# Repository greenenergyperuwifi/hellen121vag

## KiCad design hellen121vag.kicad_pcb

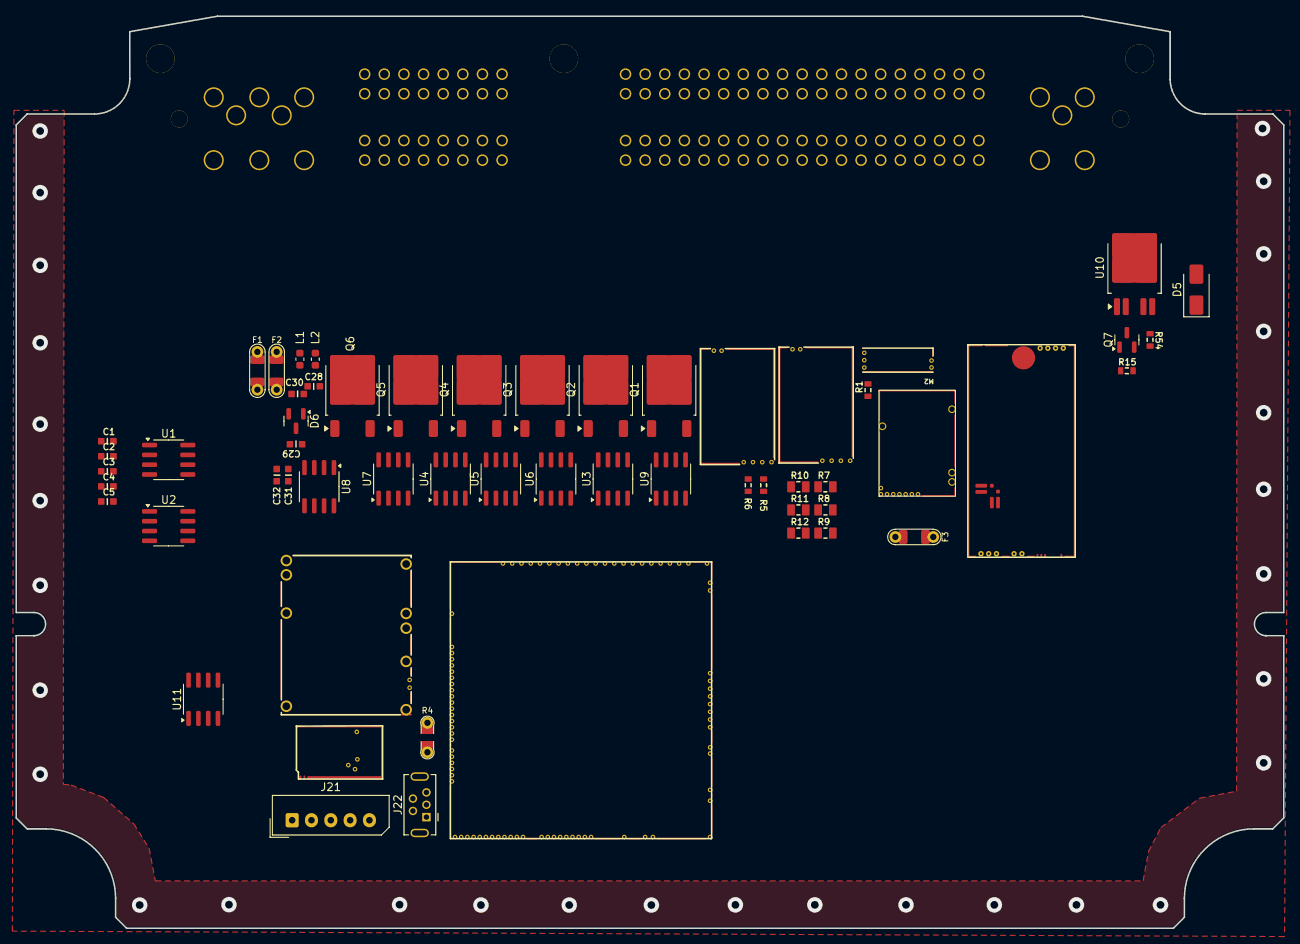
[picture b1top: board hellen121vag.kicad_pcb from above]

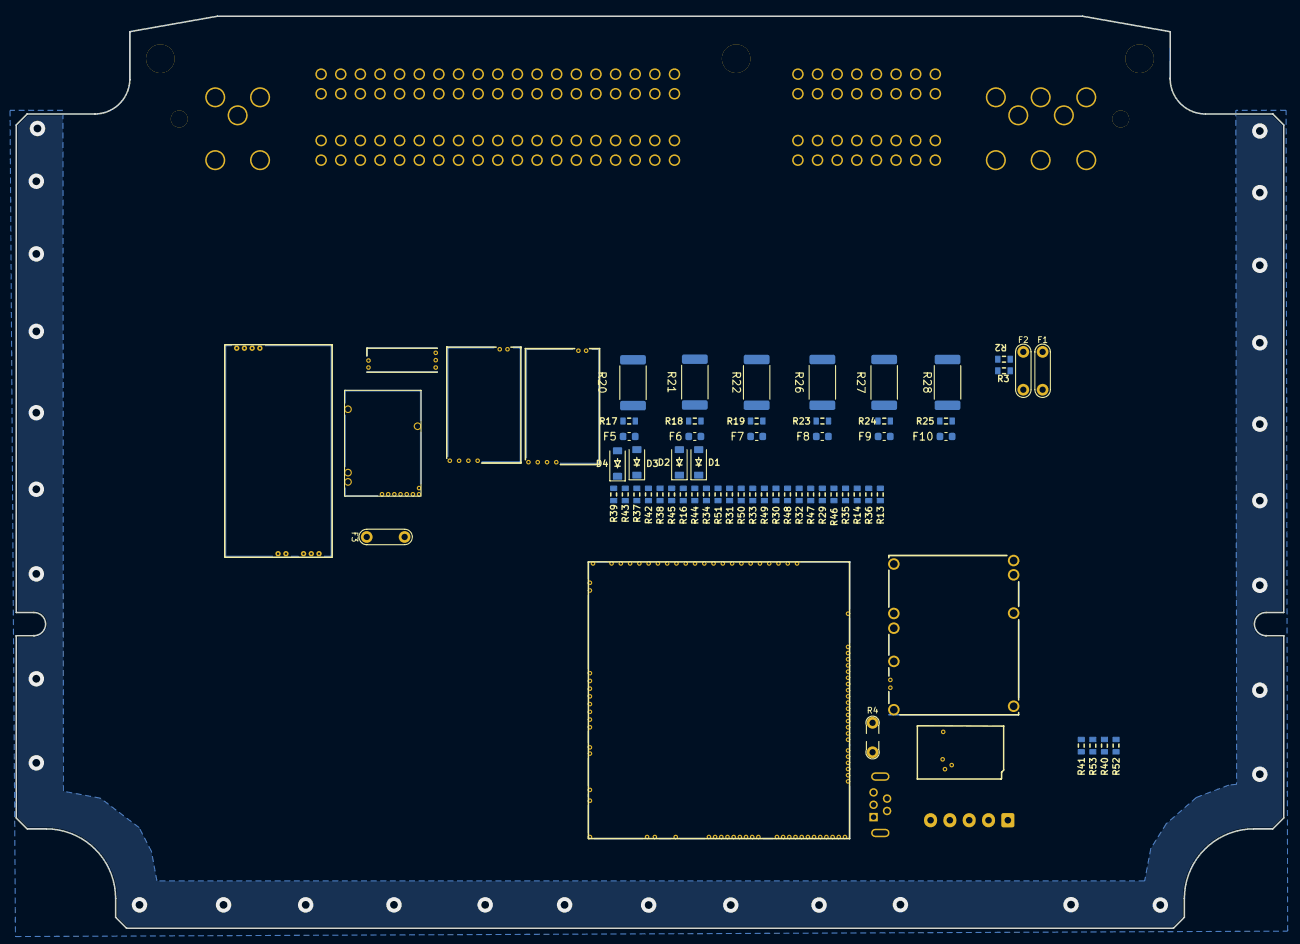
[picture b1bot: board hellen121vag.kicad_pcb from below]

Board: 4 copper layers, 164.0 x 118.0 mm, 110 parts (52 on the bottom side), 142 nets, no tracks yet.

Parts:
C1, C3, C28, C30: 10n; C0603
C2, C4, C29, C31: 100n; C0603
C5, C32: 1u; C0603
D1, D2, D3, D4: B5819W; SOD-123
D5: SS34; D_SMA
D6: NUP2105L; SOT-23
F1, F2, F3: 12H1500D; PAD-1206-PAD
F5, F6, F7, F8, F9, F10: 50mA; Fuse_0603_1608Metric
J21: Conn_01x05_Male; Molex_SPOX_5267-05A_1x05_P2.50mm_Vertical
J22: USB_B_Mini; USB-MINI-B-VERTICAL
L1, L2: 470R@100MHz; L_0603_1608Metric
M1: Module-power_12and5V-0.3; power_12and5V
M2: Module-knock-0.2; knock
M3: Module-vr-discrete-0.5; vr-discrete
M4: Module-vr-max9924-0.1; vr-max9924
M5: Module-wbo-0.5; wbo
M6: Module:mega-mcu100/0.3; mega-mcu100
M7: Module-can-0.1; can
M8: Module-motor-driver-0.1; motor-driver
P1: 368255-2
Q1, Q2, Q3, Q4, Q5: ISL9V3040D3ST; TO-252-2
Q6: AO3400A; TO-252-2
Q7: AO3400A; SOT-23
R1, R13, R14, R15, R16, R17, R29, R30, R31, R32, R33, R34, R35, R36, R37, R38, R39, R40, R41, R42, R43, R44, R45, R46, R47, R50, R51, R52, R53: 4.7k; R0603
R2: 33k; R0603
R3: 6.8k; R0603
R4: Jumper-Pad-Pad; PAD-0805-PAD
R5, R6, R19, R25: 0; R0603
R7, R8, R9: DNP; R0805
R10, R11, R12: 10k; R0805
R18, R23, R24, R48, R49: 22; R0603
R20, R21, R26, R27: 0; R_2512_6332Metric
R22: 22; R_2512_6332Metric
R28: 4.7k; R_2512_6332Metric
R54: 1k; R0603
U1, U7, U8: MAX31855KASA; SOIC-8_3.9x4.9mm_P1.27mm
U2, U3, U4, U5, U6, U9, U11: VNLD5160TR-E; SOIC-8_3.9x4.9mm_P1.27mm
U10: BTS6143D; TO-252-4

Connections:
+3.3V: M6.N21 (V33), M8.W5 (3V3_IN)
+3.3VA: C4.2, C5.2, C31.2, C32.2, M6.N15 (V33_SWITCHABLE), M7.V2 (CAN_VIO), U7.4 (V_CC), U8.4 (V_CC)
+5V: M1.E4 (V5), M6.N22 (VCC)
+5VA: M2.E1 (V5A), M3.E4 (V5_IN), M4.E4 (V5_IN), M5.W1 (V5_IN), M6.E1 (V5A_SWITCHABLE), M6.W2 (V5A_SWITCHABLE), M7.V1 (V5), R7.2, R8.2, R9.2
/ADC3: M6.S15 (IN_KNOCK_(PA2)), R5.2, R6.2
/DC1_DIR: M6.E21 (OUT_PWM4_(PC8)), M8.W4 (DIR)
/DC1_PWM: M6.E20 (OUT_PWM3_(PC7)), M8.W2 (PWM)
/EGT/SPI_CS: M6.N9 (SPI3_CS_(PA15)), U7.6 (~CS), U8.6 (~CS)
/IGN1: F5.2, M6.W10 (IGN1_(PC13))
/IGN2: F6.2, M6.W9 (IGN2_(PE5))
/IGN3: F7.2, M6.W8 (IGN3_(PE4))
/IGN4: F8.2, M6.W7 (IGN4_(PE3))
/IGN5: F9.2, M6.W6 (IGN5_(PE2))
/IGN6: F10.2, M6.W5 (IGN6_(PB8))
/INJ1: M6.E17 (OUT_INJ1_(PD3)), R34.1, R35.1
/INJ2: M6.E16 (OUT_INJ2_(PA9)), R36.1, R37.1
/INJ3: M6.E15 (OUT_INJ3_(PD11)), R38.1, R39.1
/INJ4: M6.E14 (OUT_INJ4_(PD10)), R40.1, R41.1
/INJ5: M6.E13 (OUT_INJ5_(PD2)), R42.1, R43.1, R50.1
/INJ6: M6.E12 (OUT_INJ6_(PA8)), R44.1, R45.1, R51.1
/IN_KNOCK: M2.E3 (OUT_KNOCK), R5.1
/IN_VIGN: F1.2, M1.V2 (IN_VIGN)
/IN_VMAIN: M6.S6 (IN_AUX4_(PC5)), R2.1, R3.2
/LS1: M6.E11 (OUT_INJ7_(PD15)), R16.1, R17.1
/LS2: M6.E10 (OUT_INJ8_(PD12)), R13.1, R14.1
/LS_HOT1: M6.W4 (IGN7_(PB9)), R48.1, R49.1
/LS_HOT2: M6.W3 (IGN8_(PE6)), R46.1, R47.1
/MISO3: M6.N11 (SPI3_MISO_(PC11)), U7.7 (SO), U8.7 (SO)
/PG_5VP: M6.N12 (SPI3_MOSI_(PC12)), R4.2
/PWR_EN: M1.E5 (EN_5VP), M6.N20 (OUT_PWR_EN_(PE10))
/SCK3: M6.N10 (SPI3_SCK_(PC10)), U7.5 (SCK), U8.5 (SCK)
/USB+: J21.3, J22.3 (D+), M6.N3 (USBP_(PA12))
/USB-: J21.2, J22.2 (D-), M6.N2 (USBM_(PA11))
/VBAT: M1.E1 (VBAT), M6.N17 (VBAT)
/VBUS: J21.1, J22.1 (VBUS), M6.N1 (VBUS)
/VIGN: M1.E3 (VIGN), M6.E5 (IN_VIGN_(PA5))
/VREF1: M2.W2 (VREF), M6.S22 (VREF1)
/VR_DISCRETE: M3.E3 (OUT), M6.N18 (UART8_RX_(PE0))
/VR_DISCRETE_A: M3.E2 (OUT_A), R6.1
/VR_DISCRETE_THR: M3.E1 (Thresh_IN), M6.E23 (OUT_PWM6_(PD14))
/VR_MAX9924: M4.E3 (OUT), M6.N19 (UART8_TX_(PE1))
DC1_DIS_W1: M6.E8 (SPI2_MISO_(PB14)), M8.W1 (DIS)
E6INJ7CANRX: M6.E6 (SPI2_CS_/_CAN2_RX_(PB12)), M7.V6 (CAN_RX), R30.1, R33.1, R52.1
E7INJ8CANTX: M6.E7 (SPI2_SCK_/_CAN2_TX_(PB13)), M7.V5 (CAN_TX), R31.1, R32.1, R53.1
unnamed: F3.2, M8.N2 (12V_IN), M8.S1 (12V_IN)
unnamed: F5.1, R18.2, R21.1
unnamed: F6.1, R19.2, R22.1
unnamed: F7.1, R20.2, R23.1
unnamed: F8.1, R24.2, R27.1
unnamed: F9.1, R25.2, R28.1
unnamed: F10.1, R26.2, R29.1
unnamed: M1.E6 (PG_5VP), R4.1
unnamed: M5.J1 (SEL1), M5.J_GND1 (PULL_DOWN1)
unnamed: M6.N14a (LED_GREEN), Q7.1 (G), R15.1
unnamed: Q1.1 (G), R18.1
unnamed: Q2.1 (G), R19.1
unnamed: Q3.1 (G), R20.1
unnamed: Q4.1 (G), R24.1
unnamed: Q5.1 (G), R25.1
unnamed: Q6.1 (G), R26.1
unnamed: Q7.3 (D), U10.2 (IN)
unnamed: R13.2, U1.1 (IN1)
unnamed: R16.2, U1.3 (IN2)
unnamed: R30.2, U2.1 (IN1)
unnamed: R31.2, U2.3 (IN2)
unnamed: R39.2, U3.1 (IN1)
unnamed: R40.2, U3.3 (IN2)
unnamed: R42.2, U4.1 (IN1)
unnamed: R45.2, U4.3 (IN2)
unnamed: R35.2, U5.1 (IN1)
unnamed: R37.2, U5.3 (IN2)
unnamed: R46.2, R50.2, U6.1 (IN1)
unnamed: R48.2, R51.2, U6.3 (IN2)
unnamed: C2.2, C3.2, D6.2 (K), L1.2, U7.3 (T+)
unnamed: C1.2, C2.1, D6.1 (K), L2.2, U7.2 (T-)
unnamed: C29.2, C30.2, U8.3 (T+)
unnamed: C28.2, C29.1, U8.2 (T-)
unnamed: R54.1, U10.4 (IS)
unnamed: R52.2, U11.1 (IN1)
unnamed: R53.2, U11.3 (IN2)
PIN1: M8.S3 (OUT+), P1.1
PIN2: M8.S2 (OUT-), P1.2
PIN6: M6.N14 (UART2_RX_(PD6)), P1.6
PIN7: M6.N13 (UART2_TX_(PD5)), P1.7
PIN8: P1.8, Q6.2 (C), R29.2
PIN9: P1.9, Q4.2 (C), R27.2
PIN10: P1.10, Q3.2 (C), R23.2
PIN11: P1.11, Q5.2 (C), R28.2
PIN12: P1.12, Q2.2 (C), R22.2
PIN13: P1.13, Q1.2 (C), R21.2
PIN14: D1.2 (A), P1.14, U1.6 (D2)
PIN15: D2.2 (A), P1.15, U1.8 (D1)
PIN16: D3.2 (A), P1.16, U9.8 (D1)
PIN17: M3.W2 (VR+), P1.17
PIN18: M3.W1 (VR-), P1.18
PIN19: M4.W2 (VR+), P1.19
PIN20: M4.W1 (VR-), P1.20, R1.2
PIN21: L1.1, P1.21
PIN22: L2.1, P1.22
PIN34: M6.S2 (IN_D3_(PE14)), P1.34
PIN35: M6.S3 (IN_D2_(PE13)), P1.35
PIN36: M6.S4 (IN_D1_(PE12)), P1.36
PIN37: M6.S13 (IN_MAP1_(PC0)), P1.37
PIN38: M6.S18 (IN_TPS_(PA4)), P1.38
PIN39: M6.S9 (IN_AUX1_(PB0)), P1.39
PIN40: M6.S11 (IN_O2S_/_CAN_WAKEUP_(PA0)), P1.40
PIN41: M6.S10 (IN_O2S2_(PA1)), P1.41
PIN42: M6.S17 (IN_VSS_(PE11)), P1.42
PIN43: D5.1 (K), P1.43, U10.1 (OUT), U10.5 (OUT)
PIN44: P1.44, U5.8 (D1)
PIN45: P1.45, U5.6 (D2)
PIN46: P1.46, U3.8 (D1)
PIN47: P1.47, U3.6 (D2)
PIN48: P1.48, U4.8 (D1)
PIN49: P1.49, U4.6 (D2)
PIN50: P1.50, U2.8 (D1), U11.8 (D1)
PIN51: P1.51, U2.6 (D2), U11.6 (D2)
PIN63: M6.S20 (IN_IAT_(PC3)), P1.63
PIN65: M6.S21 (IN_CLT_(PC2)), P1.65
PIN81: M2.W1 (IN_KNOCK), P1.81
PIN82: M5.W4 (CANH), M6.W11 (CANH), P1.82
PIN83: M5.W3 (CANL), M6.W12 (CANL), P1.83
PIN84: M6.S14 (IN_CRANK_(PB1)), P1.84, R7.1, R10.2
PIN85: M6.S16 (IN_CAM_(PA6)), P1.85, R8.1, R11.2
PIN86: P1.86, U6.6 (D2)
PIN87: P1.87, U6.8 (D1)
PIN88: D4.2 (A), P1.88, U9.6 (D2)
PIN89: M6.S1 (IN_D4_(PE15)), P1.89, R9.1, R12.2
PIN90: M6.S19 (IN_PPS_(PA3)), P1.90
PIN91: M6.S8 (IN_AUX2_(PC4/PE9)), P1.91
PIN102: M5.E4 (LSU_Rtrim), P1.102
PIN103: M5.E3 (LSU_Ip), P1.103
PIN104: M5.E2 (LSU_Vm), P1.104
PIN105: M5.E1 (LSU_Un), P1.105
PIN106: M1.V4 (5VP), P1.71, P1.72, P1.73, P1.74, P1.75, P1.76, P1.77, P1.78, P1.79, P1.80, P1.106, P1.107, R1.1
PIN108: F1.1, P1.108
PIN113: M6.W1 (GNDA), P1.52, P1.53, P1.54, P1.55, P1.56, P1.57, P1.58, P1.59, P1.60, P1.61, P1.62, P1.64, P1.66, P1.68, P1.98, P1.99, P1.113, R10.1, R11.1, R12.1
PIN114: C1.1, C3.1, C4.1, C5.1, C28.1, C30.1, C31.1, C32.1, D5.2 (A), D6.3 (A), J21.4, J21.5, J22.5 (GND), J22.6 (Shield), M1.S1 (GND), M2.E2 (GND), M3.G (GND), M4.G (GND), M5.E6 (LSU_H-), M5.G (GND), M6.G (GND), M7.E1 (GND), M8.G (GND), P1.3, P1.114, P1.115, Q1.3 (E), Q2.3 (E), Q3.3 (E), Q4.3 (E), Q5.3 (E), Q6.3 (E), Q7.2 (S), R3.1, R14.2, R15.2, R17.2, R32.2, R33.2, R34.2, R36.2, R38.2, R41.2, R43.2, R44.2, R47.2, R49.2, R54.2, U1.5 (S2), U1.7 (S1), U2.5 (S2), U2.7 (S1), U3.5 (S2), U3.7 (S1), U4.5 (S2), U4.7 (S1), U5.5 (S2), U5.7 (S1), U6.5 (S2), U6.7 (S1), U7.1 (GND), U8.1 (GND), U9.5 (S2), U9.7 (S1), U11.5 (S2), U11.7 (S1)
PIN116: M1.V1 (V12_PERM), P1.116
PIN117: D1.1 (K), D2.1 (K), D3.1 (K), D4.1 (K), F2.2, M1.V3 (V12_RAW), P1.117
PIN119: M5.E5 (LSU_H+), P1.119
PIN120: F2.1, F3.1, P1.23, P1.24, P1.120, R2.2, U10.3 (Vbb)

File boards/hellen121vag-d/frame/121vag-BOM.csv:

Comment,Designator,Footprint,LCSC Part #
"SS34","D5","D_SMA",""
"Conn_01x05_Male","J1","Molex_SPOX_5267-05A_1x05_P2.50mm_Vertical",""
"USB_B_Mini","J2","USB-MINI-B-VERTICAL",""
"Module:power_12and5V/0.3","M1","power_12and5V",""
"Module:knock/0.2","M2","knock",""
"Module:vr-discrete/0.5","M3","vr-discrete",""
"Module:vr-max9924/0.1","M4","vr-max9924",""
"Module:wbo/0.5","M5","wbo",""
"Module:mega-mcu100/0.3","M6","mega-mcu100",""
"Module:can/0.1","M7","can",""
"Module:motor-driver/0.1","M8","motor-driver",""
"368255-2","P1","368255-2",""
"368255-2","P2","368255-2",""
"ISL9V3040D3ST","Q1","DPAK",""
"ISL9V3040D3ST","Q2","DPAK",""
"ISL9V3040D3ST","Q3","DPAK",""
"ISL9V3040D3ST","Q4","DPAK",""
"ISL9V3040D3ST","Q5","DPAK",""
"ISL9V3040D3ST","Q6","DPAK",""
"AO3400A","Q7","SOT-23",""
"4.7k","R1","R0603",""
"0","R6","R0603",""
"DNP","R7","R0805",""
"DNP","R8","R0805",""
"DNP","R9","R0805",""
"BTS6143D","U1","TO-252-4",""
"33k","R2","R0603",""
"B5819W","D1","SOD-123",""
"B5819W","D2","SOD-123",""
"B5819W","D3","SOD-123",""
"B5819W","D4","SOD-123",""
"100n","C2","C0603",""
"100n","C4","C0603",""
"1u","C5","C0603",""
"10k","R10","R0805",""
"10k","R11","R0805",""
"10k","R12","R0805",""
"Jumper-Pad-Pad","R4","PAD-0805-PAD",""
"0","R5","R0603",""
"4.7k","R15","R0603",""
"4.7k","R13","R0603",""
"4.7k","R14","R0603",""
"4.7k","R16","R0603",""
"4.7k","R29","R0603",""
"4.7k","R30","R0603",""
"4.7k","R31","R0603",""
"4.7k","R32","R0603",""
"4.7k","R33","R0603",""
"4.7k","R34","R0603",""
"4.7k","R35","R0603",""
"4.7k","R36","R0603",""
"4.7k","R37","R0603",""
"4.7k","R38","R0603",""
"4.7k","R39","R0603",""
"4.7k","R40","R0603",""
"4.7k","R41","R0603",""
"4.7k","R42","R0603",""
"4.7k","R43","R0603",""
"4.7k","R44","R0603",""
"4.7k","R45","R0603",""
"4.7k","R46","R0603",""
"4.7k","R47","R0603",""
"4.7k","R48","R0603",""
"4.7k","R49","R0603",""
"4.7k","R50","R0603",""
"6.8k","R3","R0603",""
"22","R17","R0603",""
"22","R18","R0603",""
"22","R19","R0603",""
"22","R23","R0603",""
"22","R24","R0603",""
"22","R25","R0603",""
"0","R20","R2512",""
"0","R21","R2512",""
"0","R22","R2512",""
"0","R26","R2512",""
"0","R27","R2512",""
"0","R28","R2512",""
"MAX31855KASA","U2","SO8",""
"MAX31855KASA","U8","SO8",""
"10n","C1","C0603",""
"10n","C3","C0603",""
"470R@100MHz","L1","L_0603_1608Metric",""
"470R@100MHz","L2","L_0603_1608Metric",""
"12H1500D","F1","PAD-1206-PAD",""
"12H1500D","F2","PAD-1206-PAD",""
"12H1500D","F3","PAD-1206-PAD",""
"NUP2105L","D6","SOT-23",""
"50mA","F5","Fuse_0603_1608Metric",""
"50mA","F6","Fuse_0603_1608Metric",""
"50mA","F7","Fuse_0603_1608Metric",""
"50mA","F8","Fuse_0603_1608Metric",""
"50mA","F9","Fuse_0603_1608Metric",""
"50mA","F10","Fuse_0603_1608Metric",""
"VNLD5160TR-E","U3","SO8",""
"VNLD5160TR-E","U4","SO8",""
"VNLD5160TR-E","U5","SO8",""
"VNLD5160TR-E","U6","SO8",""
"VNLD5160TR-E","U7","SO8",""

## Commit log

2025-12-14 [skip actions] Auto-generated board
2025-12-14 Update hellen-one submodule to my fork with motor-driver
2025-12-14 [skip actions] Auto-generated board v2.1
2025-12-17 awsw
2025-12-17 wwew
